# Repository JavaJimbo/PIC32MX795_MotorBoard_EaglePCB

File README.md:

# PIC32MX795_MotorBoard_EaglePCB
Motor Control board with four 6 Amp H bridges to use as daughter board with PIC32MX795 BrainBoard

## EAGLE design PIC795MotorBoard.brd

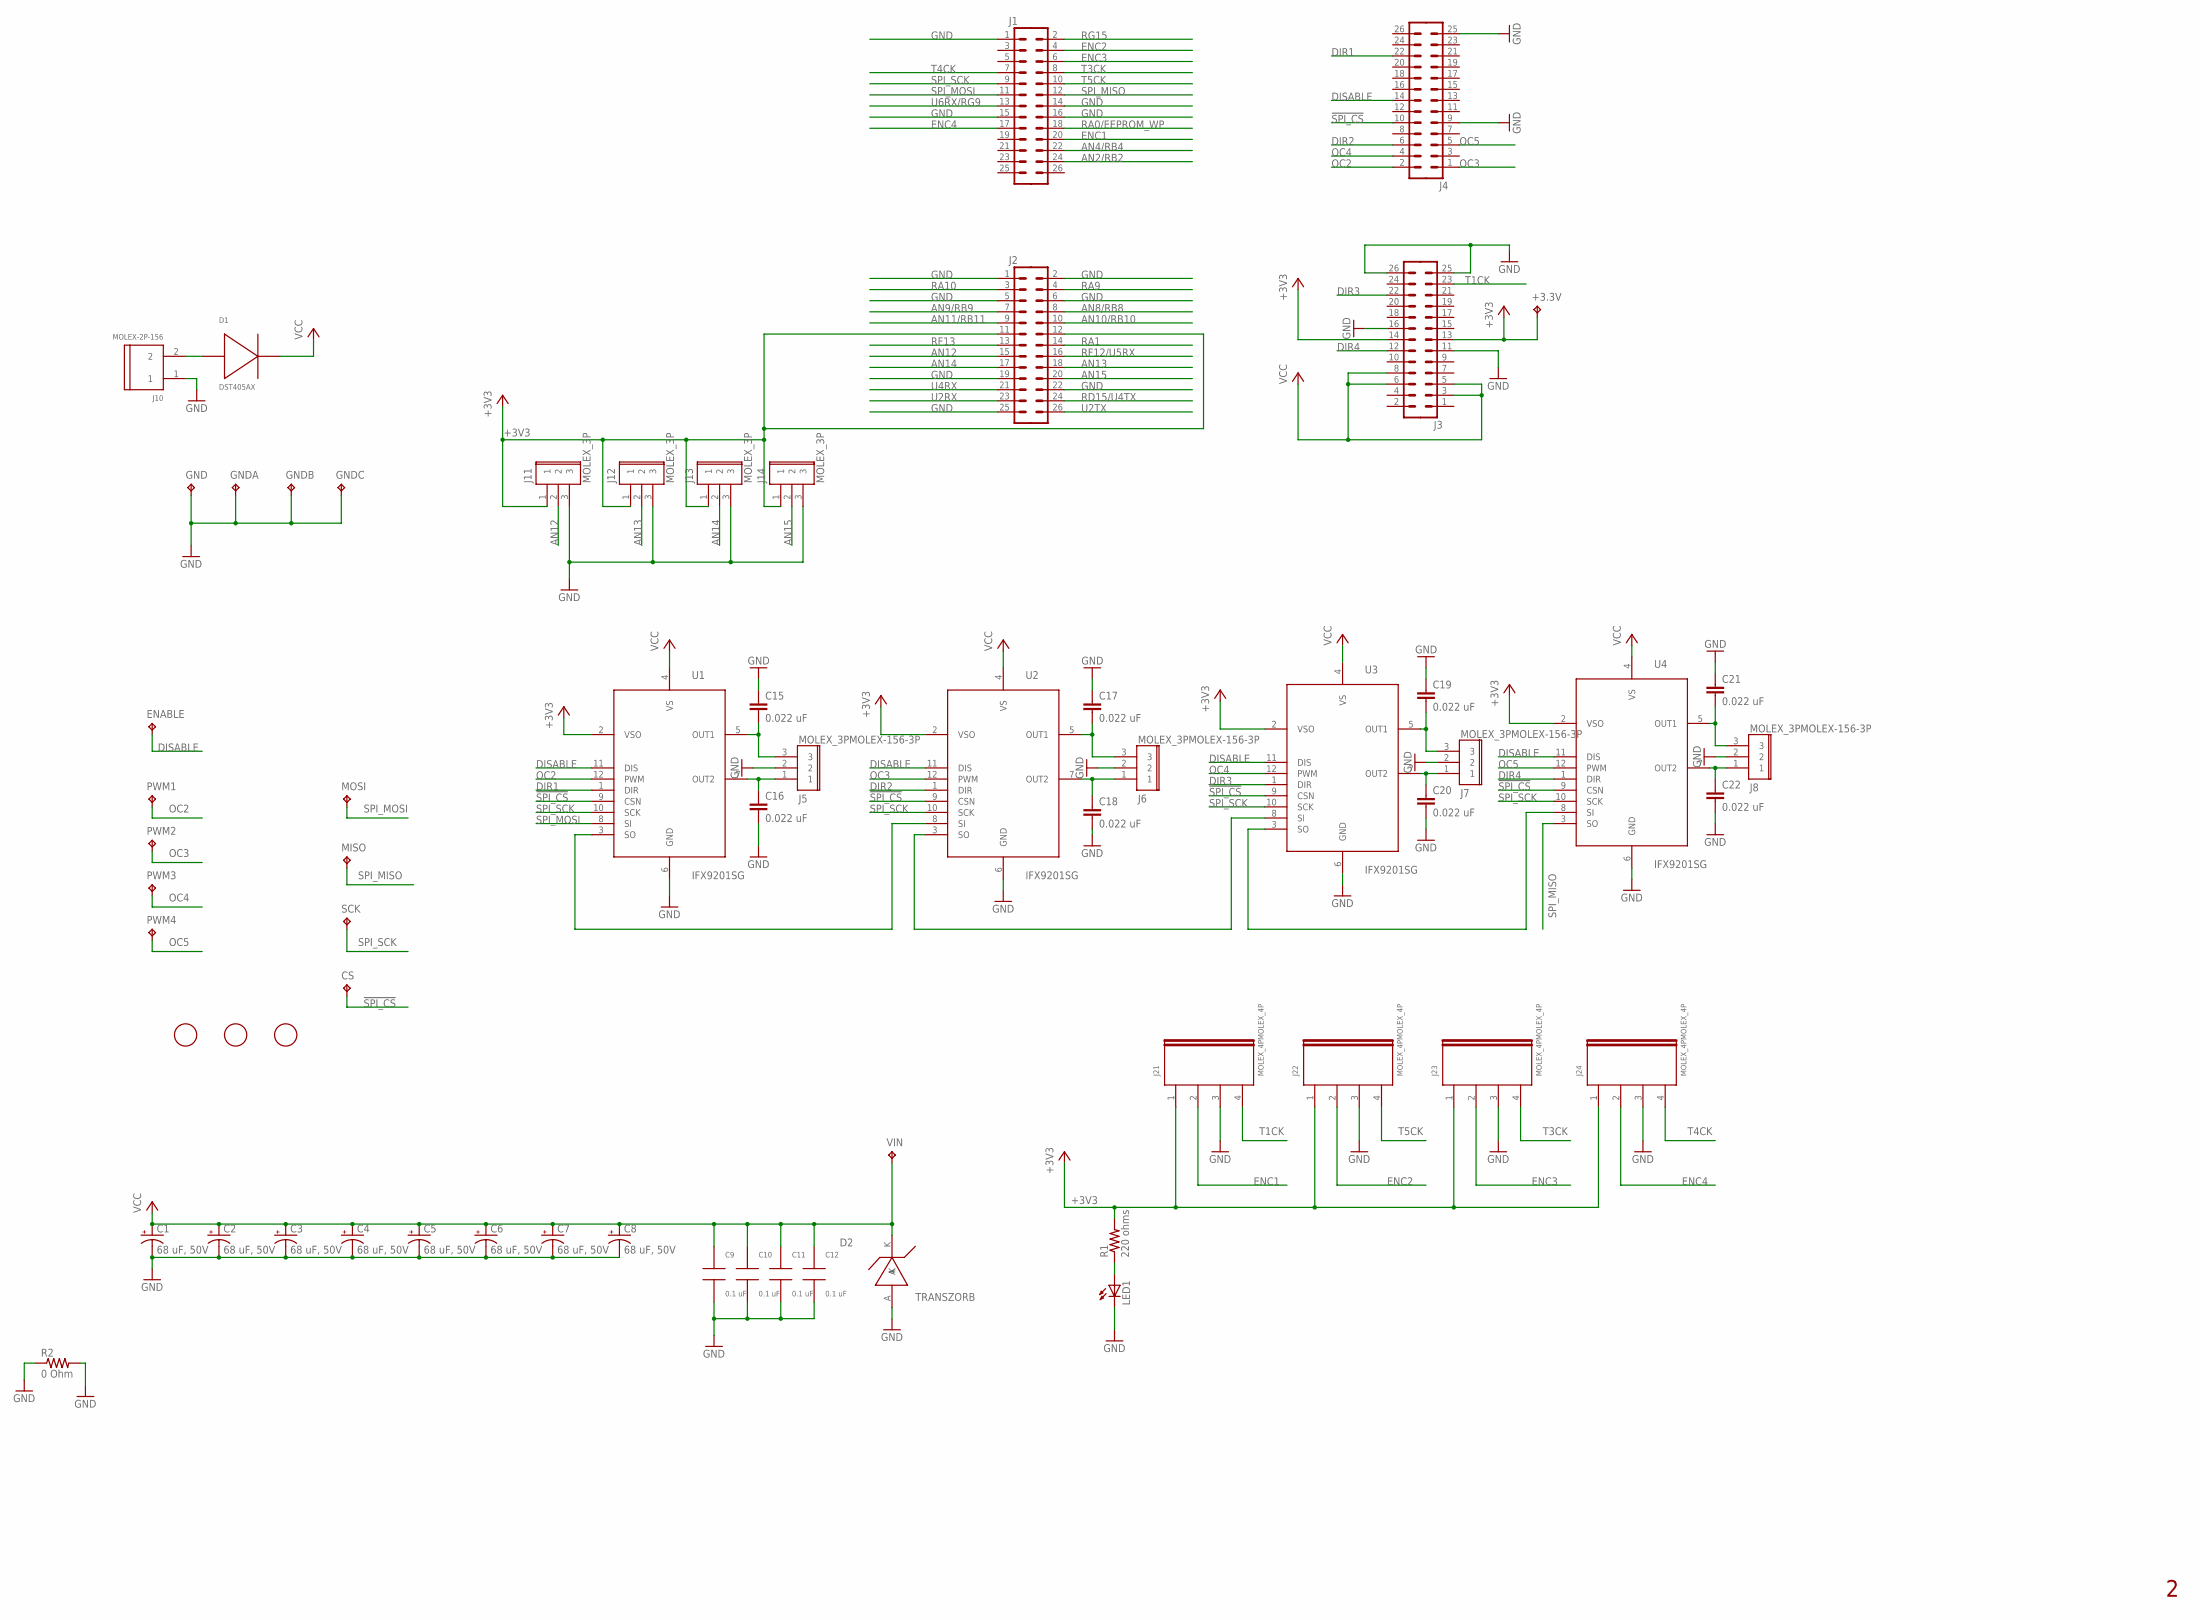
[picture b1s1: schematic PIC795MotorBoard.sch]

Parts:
+3.3V: TP; TESTPAD
C1, C2, C3, C4, C5, C6, C7, C8: 68 uF, 50V; E3,5-10
C9, C10, C11, C12: 0.1 uF; C0.3
C15, C16, C17, C18, C19, C20, C21, C22: 0.022 uF; C5B2.5
CS: TPTESTPAD-SMALL; TESTPAD-SMALL
D1: DST405AX; DIODE_10A_THRU
D2: TRANSZORB; P600
ENABLE: TPTESTPAD-SMALL; TESTPAD-SMALL
GND: TP; TESTPAD
GNDA: TP; TESTPAD
GNDB: TP; TESTPAD
GNDC: TP; TESTPAD
J1, J2, J3, J4: M13X22X13; 2X13
J5, J6, J7, J8: MOLEX_3PMOLEX-156-3P; MOLEX-156-3
J10: MOLEX-2P-156; MOLEX-156-2P
J11, J12, J13, J14: MOLEX_3P
J21, J22, J23, J24: MOLEX_4PMOLEX_4P; MOLEX_4P
LED1: LED5MM
MISO: TPTESTPAD-SMALL; TESTPAD-SMALL
MOSI: TPTESTPAD-SMALL; TESTPAD-SMALL
PWM1, PWM2, PWM3, PWM4: TPTESTPAD-SMALL; TESTPAD-SMALL
R1: 220 ohms; 0204/5
R2: 0 Ohm; R0402
SCK: TPTESTPAD-SMALL; TESTPAD-SMALL
U1, U2, U3, U4: IFX9201SG
U$1, U$2, U$3: FIDUCIAL; FIDUCIAL_1MM
VIN: TP; TESTPAD

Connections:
!SPI_CS: CS.P$1, J4.10, U1.9 (CSN), U2.9 (CSN), U3.9 (CSN), U4.9 (CSN)
+3V3: +3.3V.P$1, J2.11, J2.12, J3.13, J3.14, J11.1, J12.1, J13.1, J14.1, J21.1, J22.1, J23.1, J24.1, R1.2, U1.2 (VSO), U2.2 (VSO), U3.2 (VSO), U4.2 (VSO)
AN2/RB2: J1.24
AN4/RB4: J1.22
AN8/RB8: J2.8
AN9/RB9: J2.7
AN10/RB10: J2.10
AN11/RB11: J2.9
AN12: J2.15, J11.2
AN13: J2.18, J12.2
AN14: J2.17, J13.2
AN15: J2.20, J14.2
DIR1: J4.22, U1.1 (DIR)
DIR2: J4.6, U2.1 (DIR)
DIR3: J3.22, U3.1 (DIR)
DIR4: J3.12, U4.1 (DIR)
DISABLE: ENABLE.P$1, J4.14, U1.11 (DIS), U2.11 (DIS), U3.11 (DIS), U4.11 (DIS)
ENC1: J1.20, J21.2
ENC2: J1.4, J22.2
ENC3: J1.6, J23.2
ENC4: J1.17, J24.2
GND: C1.-, C2.-, C3.-, C4.-, C5.-, C6.-, C7.-, C8.-, C9.2 (1), C10.2 (1), C11.2 (1), C12.2 (1), C15.1, C16.2, C17.1, C18.2, C19.1, C20.2, C21.1, C22.2, D2.A, GND.P$1, GNDA.P$1, GNDB.P$1, GNDC.P$1, J1.1, J1.14, J1.15, J1.16, J2.1, J2.2, J2.5, J2.6, J2.19, J2.22, J2.25, J3.11, J3.16, J3.25, J3.26, J4.9, J4.25, J5.2, J6.2, J7.2, J8.2, J10.1, J11.3, J12.3, J13.3, J14.3, J21.3, J22.3, J23.3, J24.3, LED1.K (C), R2.1, R2.2, U1.6 (GND), U2.6 (GND), U3.6 (GND), U4.6 (GND)
unnamed: D1.P$1 (ANODE), J10.2
unnamed: U1.3 (SO), U2.8 (SI)
unnamed: U2.3 (SO), U3.8 (SI)
unnamed: U3.3 (SO), U4.8 (SI)
unnamed: C16.1, J5.1, U1.7 (OUT2)
unnamed: C15.2, J5.3, U1.5 (OUT1)
unnamed: C18.1, J6.1, U2.7 (OUT2)
unnamed: C17.2, J6.3, U2.5 (OUT1)
unnamed: C20.1, J7.1, U3.7 (OUT2)
unnamed: C19.2, J7.3, U3.5 (OUT1)
unnamed: C22.1, J8.1, U4.7 (OUT2)
unnamed: C21.2, J8.3, U4.5 (OUT1)
unnamed: LED1.A, R1.1
OC2: J4.2, PWM1.P$1, U1.12 (PWM)
OC3: J4.1, PWM2.P$1, U2.12 (PWM)
OC4: J4.4, PWM3.P$1, U3.12 (PWM)
OC5: J4.5, PWM4.P$1, U4.12 (PWM)
RA0/EEPROM_WP: J1.18
RA1: J2.14
RA9: J2.4
RA10: J2.3
RD15/U4TX: J2.24
RF12/U5RX: J2.16
RF13: J2.13
RG15: J1.2
SPI_MISO: J1.12, MISO.P$1, U4.3 (SO)
SPI_MOSI: J1.11, MOSI.P$1, U1.8 (SI)
SPI_SCK: J1.9, SCK.P$1, U1.10 (SCK), U2.10 (SCK), U3.10 (SCK), U4.10 (SCK)
T1CK: J3.23, J21.4
T3CK: J1.8, J23.4
T4CK: J1.7, J24.4
T5CK: J1.10, J22.4
U2RX: J2.23
U2TX: J2.26
U4RX: J2.21
U6RX/RG9: J1.13
VCC: C1.+, C2.+, C3.+, C4.+, C5.+, C6.+, C7.+, C8.+, C9.1 (2), C10.1 (2), C11.1 (2), C12.1 (2), D1.P$2 (CATHODE), D2.K, J3.3, J3.5, J3.6, J3.8, U1.4 (VS), U2.4 (VS), U3.4 (VS), U4.4 (VS), VIN.P$1

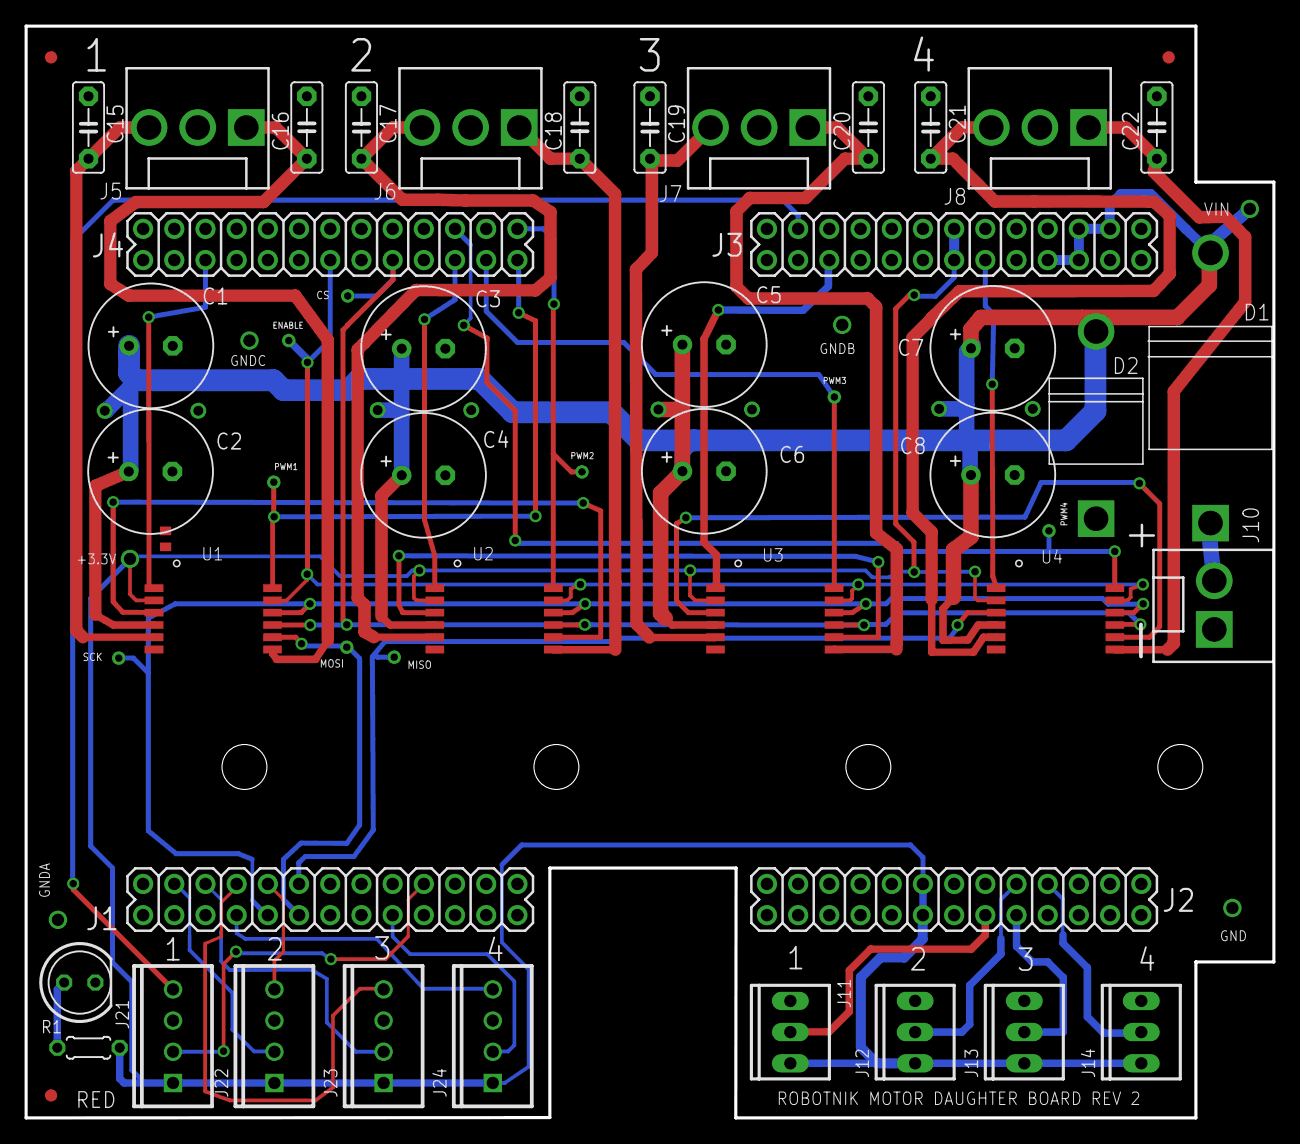
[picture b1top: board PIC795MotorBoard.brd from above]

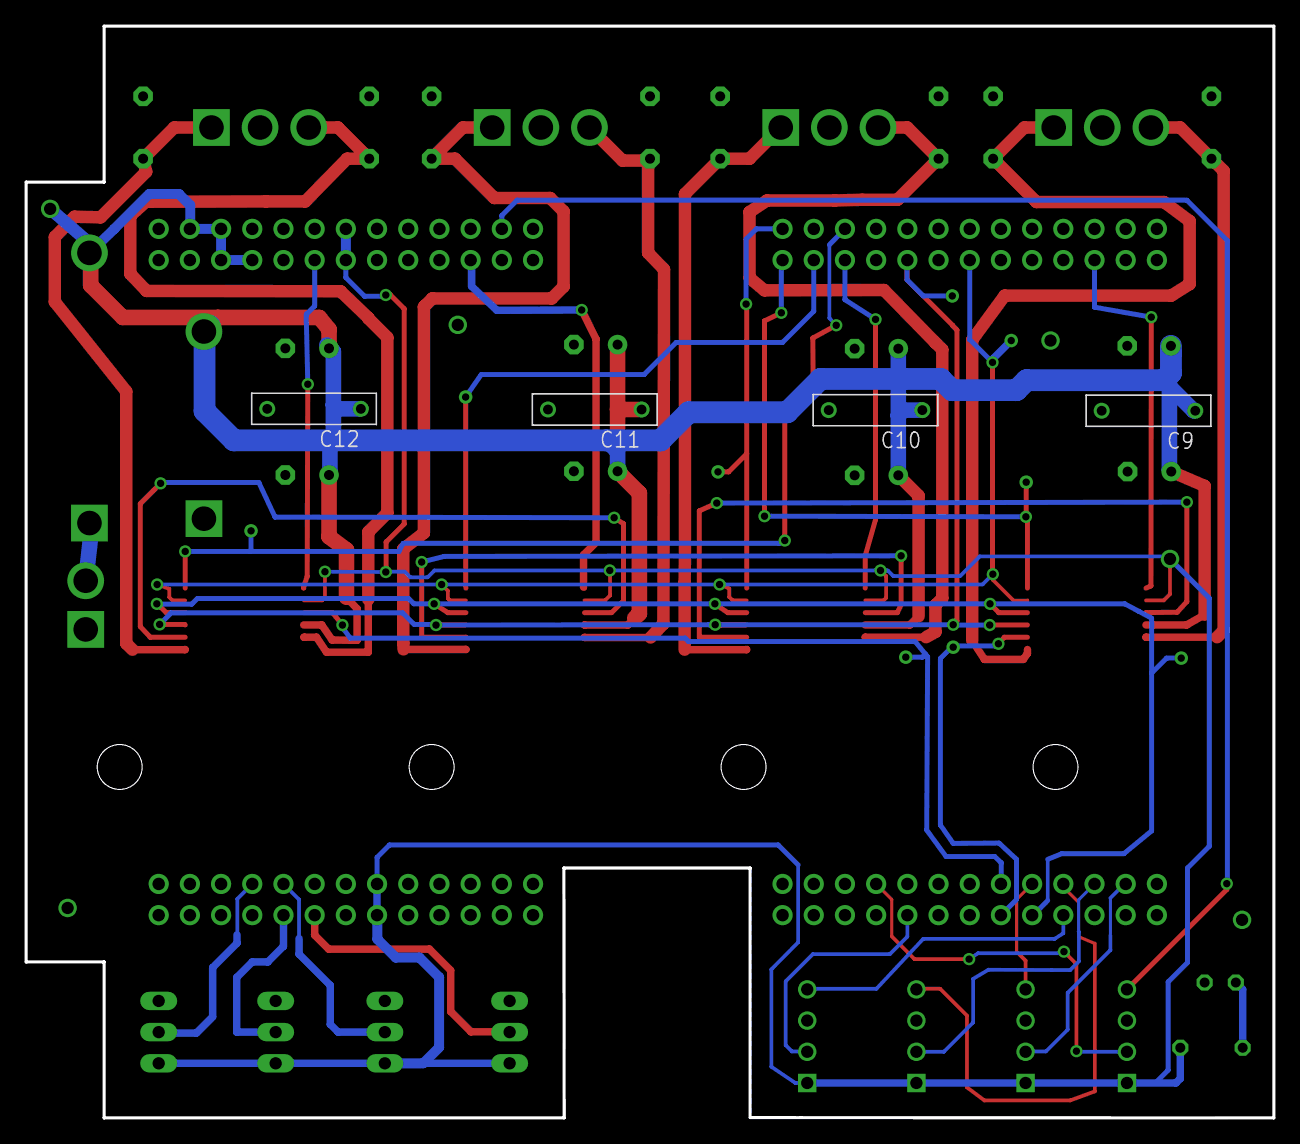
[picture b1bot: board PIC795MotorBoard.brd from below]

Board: 2 copper layers, 101.6 x 88.9 mm, 64 parts (4 on the bottom side), 41 nets.

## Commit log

2019-07-21 Add files via upload
    This is REV 2 - minor corrections made to Rev 1 - eliminated 5V DC regulator.
2019-08-12 Rev 2 board sent to PCB fab 8-11-19

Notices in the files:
parts and their libraries:
SparkFun-Connectors: Licensing: Creative Commons ShareAlike 4.0 International - https://creativecommons.org/licenses/by-sa/4.0
